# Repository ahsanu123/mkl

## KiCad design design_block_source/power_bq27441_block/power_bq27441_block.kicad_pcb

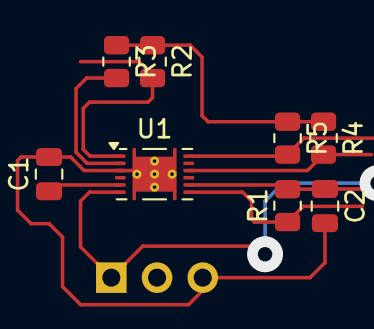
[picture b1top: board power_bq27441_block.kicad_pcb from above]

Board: 2 copper layers, 9 parts (1 on the bottom side), 9 nets.

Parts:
C1: 470nF; C_0805_2012Metric
C2: 1uF; C_0805_2012Metric
J1: BattConn; PinSocket_1x03_P2.54mm_Vertical
R1: 10m 1%; R_0805_2012Metric
R2, R3, R5: 5K1; R_0805_2012Metric
R4: 1M8; R_0805_2012Metric
U1: BQ27441-G1; Texas_S-PDSO-N12

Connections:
+3.3V: R2.1, R3.1, R4.1, R5.1
+BATT: C2.1, J1.1, R1.2, U1.6 (BAT), U1.8 (SRP)
/BIN: R4.2, U1.10 (BIN)
/GPOUT: R5.2, U1.12 (GPOUT)
/SCL: R3.2, U1.2 (SCL)
/SDA: R2.2, U1.1 (SDA)
GND: C1.2, C2.2, J1.3, U1.3 (V_{SS}), U1.13 (PAD)
unnamed: C1.1, U1.5 (V_{DD})
VSys: R1.1, U1.7 (SRN)
